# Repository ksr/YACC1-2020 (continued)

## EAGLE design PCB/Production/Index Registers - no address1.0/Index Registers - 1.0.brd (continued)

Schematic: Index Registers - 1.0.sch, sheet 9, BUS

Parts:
PWR: LED5MM
R1: 330; 0207/10
X1: FABC96R

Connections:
-AC-LD: X1.C22
-AC-LD-INV: X1.C20
-AC-RD: X1.C21
-ADDR-REG-LD0: X1.C4
-ADDR-REG-LD1: X1.C6
-ADDR-REG-RD0: X1.C3
-ADDR-REG-RD1: X1.C5
-ALU-FUNC: X1.C15
-BUS-EN: X1.C28; also elsewhere on the board
-HL-SWAP: X1.C25; also elsewhere on the board
-INT: X1.C13
-INTA: X1.C14
-IO-ADDR-LD: X1.C11
-IO-RD: X1.B25
-IO-WR: X1.B26
-MEM-RD: X1.B23
-MEM-WR: X1.B24
-REG-DN: X1.B21; also elsewhere on the board
-REG-FUNC-LD: X1.B8; also elsewhere on the board
-REG-FUNC-RD: X1.B7; also elsewhere on the board
-REG-LD-HI: X1.B20; also elsewhere on the board
-REG-LD-LO: X1.B18; also elsewhere on the board
-REG-RD-HI: X1.B19; also elsewhere on the board
-REG-RD-LO: X1.B17; also elsewhere on the board
-REG-UP: X1.B22; also elsewhere on the board
-RESET: X1.C30; also elsewhere on the board
-RUN: X1.C29
-SR-LD: X1.C23
-TMP-REG-LD0: X1.B28
-TMP-REG-LD1: X1.B30
-TMP-REG-RD0: X1.B27
-TMP-REG-RD1: X1.B29
ADDR0: X1.A3
ADDR1: X1.A4
ADDR2: X1.A5
ADDR3: X1.A6
ADDR4: X1.A7
ADDR5: X1.A8
ADDR6: X1.A9
ADDR7: X1.A10
ADDR8: X1.A11
ADDR9: X1.A12
ADDR10: X1.A13
ADDR11: X1.A14
ADDR12: X1.A15
ADDR13: X1.A16
ADDR14: X1.A17
ADDR15: X1.A18
ALU0: X1.C16
ALU1: X1.C17
ALU2: X1.C18
ALU3: X1.C19
BR-COND: X1.C24
DATA0: X1.A19; also elsewhere on the board
DATA1: X1.A20; also elsewhere on the board
DATA2: X1.A21; also elsewhere on the board
DATA3: X1.A22; also elsewhere on the board
DATA4: X1.A23; also elsewhere on the board
DATA5: X1.A24; also elsewhere on the board
DATA6: X1.A25; also elsewhere on the board
DATA7: X1.A26; also elsewhere on the board
DATA8: X1.A27; also elsewhere on the board
DATA9: X1.A28; also elsewhere on the board
DATA10: X1.A29; also elsewhere on the board
DATA11: X1.A30; also elsewhere on the board
DATA12: X1.B3; also elsewhere on the board
DATA13: X1.B4; also elsewhere on the board
DATA14: X1.B5; also elsewhere on the board
DATA15: X1.B6; also elsewhere on the board
GND: PWR.K (C), X1.A1, X1.A32, X1.B1, X1.B32, X1.C1, X1.C32; also elsewhere on the board
IN: X1.C26
IO-ADDR0: X1.C7
IO-ADDR1: X1.C8
IO-ADDR2: X1.C9
IO-ADDR3: X1.C10
unnamed: PWR.A, R1.1
OUT: X1.C27
REG-LD-ID0: X1.B13; also elsewhere on the board
REG-LD-ID1: X1.B14; also elsewhere on the board
REG-LD-ID2: X1.B15; also elsewhere on the board
REG-LD-ID3: X1.B16; also elsewhere on the board
REG-RD-ID0: X1.B9; also elsewhere on the board
REG-RD-ID1: X1.B10; also elsewhere on the board
REG-RD-ID2: X1.B11; also elsewhere on the board
REG-RD-ID3: X1.B12; also elsewhere on the board
UNUSED0: X1.C12
VCC: R1.2, X1.A2, X1.A31, X1.B2, X1.B31, X1.C2, X1.C31; also elsewhere on the board

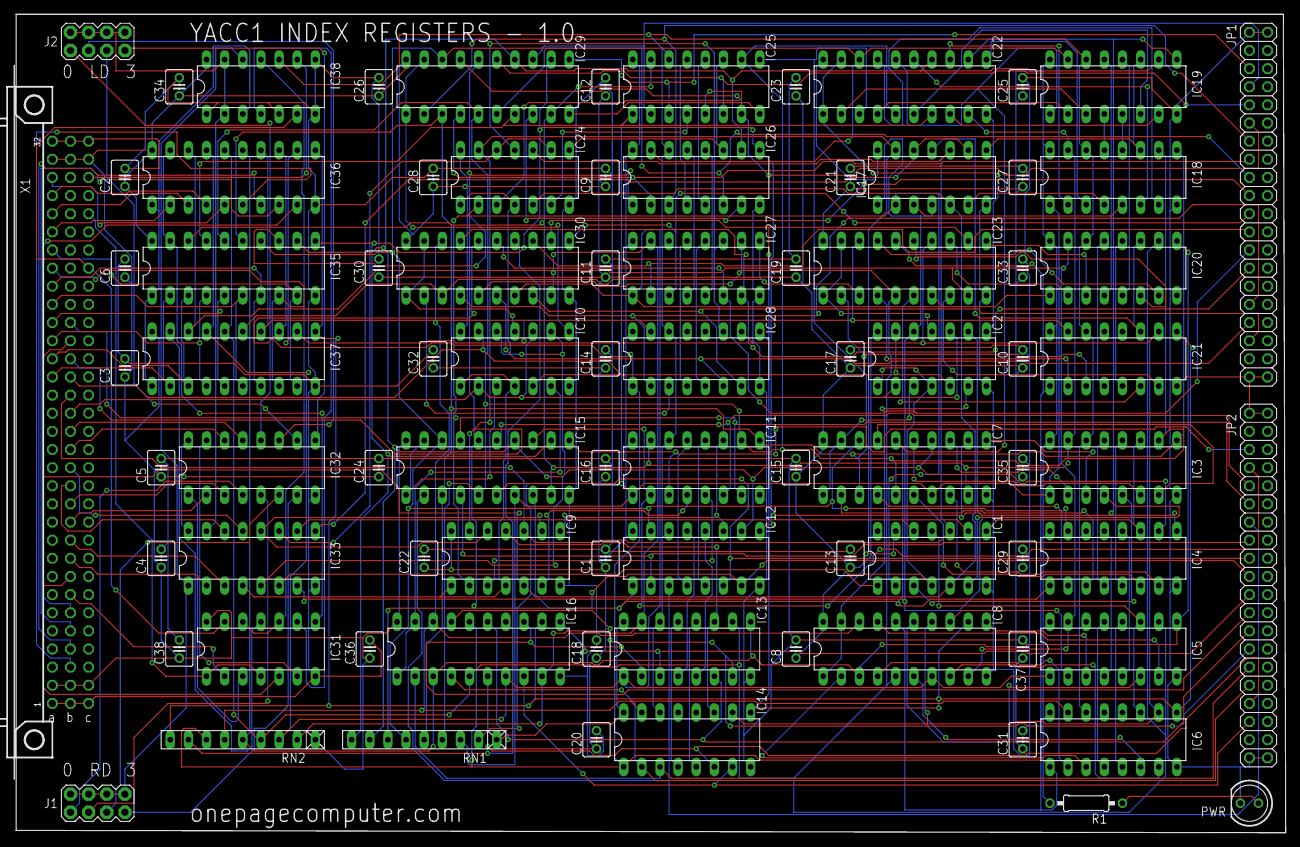
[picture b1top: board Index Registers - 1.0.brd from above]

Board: 2 copper layers, 177.8 x 114.6 mm, 83 parts (0 on the bottom side), 192 nets.

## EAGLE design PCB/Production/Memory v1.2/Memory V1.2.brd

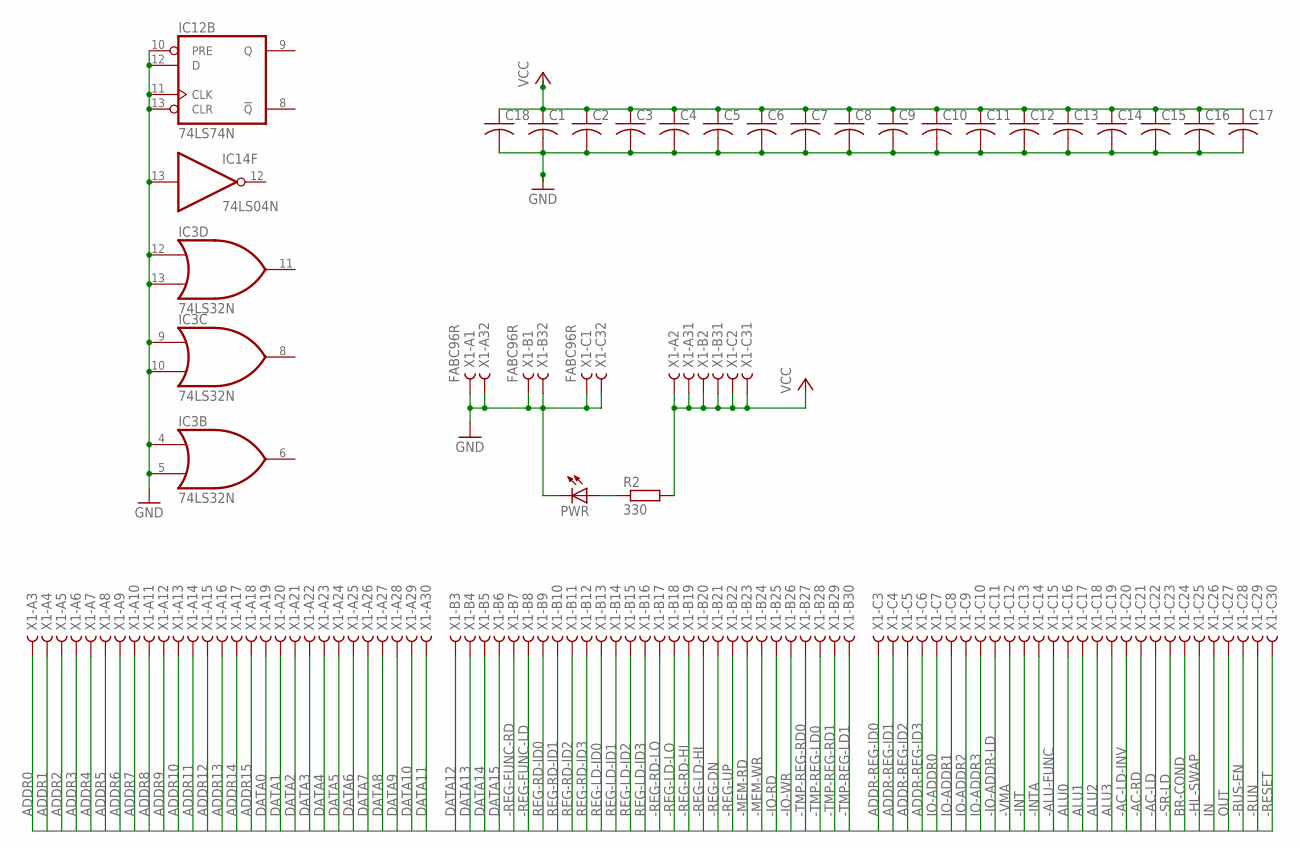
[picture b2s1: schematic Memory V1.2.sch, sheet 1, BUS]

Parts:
C1, C2, C3, C4, C5, C6, C7, C8, C9, C10, C11, C12, C13, C14, C15, C16, C17, C18: C-US025-025X050; C025-025X050
IC3: 74LS32N; DIL14
IC12: 74LS74N; DIL14
IC14: 74LS04N; DIL14
PWR: LED5MM
R2: 330; 0207/10
X1: FABC96R

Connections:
-AC-LD: X1.C22
-AC-LD-INV: X1.C20
-AC-RD: X1.C21
-ALU-FUNC: X1.C15
-BUS-EN: X1.C28; also elsewhere on the board
-HL-SWAP: X1.C25
-INT: X1.C13
-INTA: X1.C14
-IO-ADDR-LD: X1.C11
-IO-RD: X1.B25
-IO-WR: X1.B26
-MEM-RD: X1.B23; also elsewhere on the board
-MEM-WR: X1.B24; also elsewhere on the board
-REG-DN: X1.B21
-REG-FUNC-LD: X1.B8
-REG-FUNC-RD: X1.B7
-REG-LD-HI: X1.B20
-REG-LD-LO: X1.B18
-REG-RD-HI: X1.B19
-REG-RD-LO: X1.B17
-REG-UP: X1.B22
-RESET: X1.C30; also elsewhere on the board
-RUN: X1.C29
-SR-LD: X1.C23
-TMP-REG-LD0: X1.B28; also elsewhere on the board
-TMP-REG-LD1: X1.B30; also elsewhere on the board
-TMP-REG-RD0: X1.B27; also elsewhere on the board
-TMP-REG-RD1: X1.B29; also elsewhere on the board
-VMA: X1.C12; also elsewhere on the board
ADDR0: X1.A3; also elsewhere on the board
ADDR1: X1.A4; also elsewhere on the board
ADDR2: X1.A5; also elsewhere on the board
ADDR3: X1.A6; also elsewhere on the board
ADDR4: X1.A7; also elsewhere on the board
ADDR5: X1.A8; also elsewhere on the board
ADDR6: X1.A9; also elsewhere on the board
ADDR7: X1.A10; also elsewhere on the board
ADDR8: X1.A11; also elsewhere on the board
ADDR9: X1.A12; also elsewhere on the board
ADDR10: X1.A13; also elsewhere on the board
ADDR11: X1.A14; also elsewhere on the board
ADDR12: X1.A15; also elsewhere on the board
ADDR13: X1.A16; also elsewhere on the board
ADDR14: X1.A17; also elsewhere on the board
ADDR15: X1.A18; also elsewhere on the board
ADDR-REG-ID0: X1.C3
ADDR-REG-ID1: X1.C4
ADDR-REG-ID2: X1.C5
ADDR-REG-ID3: X1.C6
ALU0: X1.C16
ALU1: X1.C17
ALU2: X1.C18
ALU3: X1.C19
BR-COND: X1.C24
DATA0: X1.A19; also elsewhere on the board
DATA1: X1.A20; also elsewhere on the board
DATA2: X1.A21; also elsewhere on the board
DATA3: X1.A22; also elsewhere on the board
DATA4: X1.A23; also elsewhere on the board
DATA5: X1.A24; also elsewhere on the board
DATA6: X1.A25; also elsewhere on the board
DATA7: X1.A26; also elsewhere on the board
DATA8: X1.A27; also elsewhere on the board
DATA9: X1.A28; also elsewhere on the board
DATA10: X1.A29; also elsewhere on the board
DATA11: X1.A30; also elsewhere on the board
DATA12: X1.B3; also elsewhere on the board
DATA13: X1.B4; also elsewhere on the board
DATA14: X1.B5; also elsewhere on the board
DATA15: X1.B6; also elsewhere on the board
GND: C1.2, C2.2, C3.2, C4.2, C5.2, C6.2, C7.2, C8.2, C9.2, C10.2, C11.2, C12.2, C13.2, C14.2, C15.2, C16.2, C17.2, C18.2, IC3.4 (I0), IC3.5 (I1), IC3.7 (GND), IC3.9 (I0), IC3.10 (I1), IC3.12 (I0), IC3.13 (I1), IC12.7 (GND), IC12.10 (PRE), IC12.11 (CLK), IC12.12 (D), IC12.13 (CLR), IC14.7 (GND), IC14.13 (I), PWR.K (C), X1.A1, X1.A32, X1.B1, X1.B32, X1.C1, X1.C32; also elsewhere on the board
IN: X1.C26
IO-ADDR0: X1.C7
IO-ADDR1: X1.C8
IO-ADDR2: X1.C9
IO-ADDR3: X1.C10
unnamed: PWR.A, R2.1
OUT: X1.C27
REG-LD-ID0: X1.B13
REG-LD-ID1: X1.B14
REG-LD-ID2: X1.B15
REG-LD-ID3: X1.B16
REG-RD-ID0: X1.B9
REG-RD-ID1: X1.B10
REG-RD-ID2: X1.B11
REG-RD-ID3: X1.B12
VCC: C1.1, C2.1, C3.1, C4.1, C5.1, C6.1, C7.1, C8.1, C9.1, C10.1, C11.1, C12.1, C13.1, C14.1, C15.1, C16.1, C17.1, C18.1, IC3.14 (VCC), IC12.14 (VCC), IC14.14 (VCC), R2.2, X1.A2, X1.A31, X1.B2, X1.B31, X1.C2, X1.C31; also elsewhere on the board

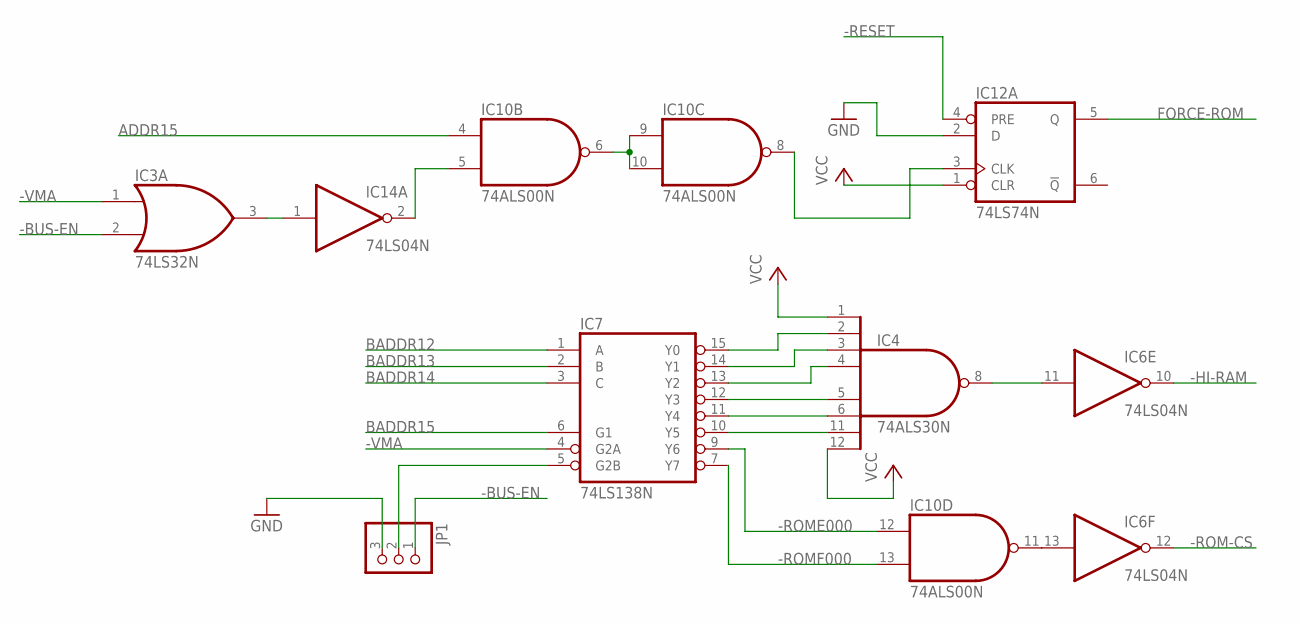
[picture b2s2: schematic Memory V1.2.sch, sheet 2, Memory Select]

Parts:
IC3: 74LS32N; DIL14
IC4: 74ALS30N; DIL14
IC6, IC14: 74LS04N; DIL14
IC7: 74LS138N; DIL16
IC10: 74ALS00N; DIL14
IC12: 74LS74N; DIL14
JP1: PINHD-1X3; 1X03

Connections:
-BUS-EN: IC3.2 (I1), JP1.1; also elsewhere on the board
-HI-RAM: IC6.10 (O); also elsewhere on the board
-RESET: IC12.4 (PRE); also elsewhere on the board
-ROM-CS: IC6.12 (O); also elsewhere on the board
-ROME000: IC7.9 (Y6), IC10.12 (I0)
-ROMF000: IC7.7 (Y7), IC10.13 (I1)
-VMA: IC3.1 (I0), IC7.4 (G2A); also elsewhere on the board
ADDR15: IC10.4 (I0); also elsewhere on the board
BADDR12: IC7.1 (A); also elsewhere on the board
BADDR13: IC7.2 (B); also elsewhere on the board
BADDR14: IC7.3 (C); also elsewhere on the board
BADDR15: IC7.6 (G1); also elsewhere on the board
FORCE-ROM: IC12.5 (Q); also elsewhere on the board
GND: IC3.7 (GND), IC4.7 (GND), IC6.7 (GND), IC7.8 (GND), IC10.7 (GND), IC12.2 (D), IC12.7 (GND), IC14.7 (GND), JP1.3; also elsewhere on the board
unnamed: IC6.13 (I), IC10.11 (O)
unnamed: IC4.11 (I6), IC7.10 (Y5)
unnamed: IC4.6 (I5), IC7.11 (Y4)
unnamed: IC4.5 (I4), IC7.12 (Y3)
unnamed: IC4.4 (I3), IC7.13 (Y2)
unnamed: IC4.3 (I2), IC7.14 (Y1)
unnamed: IC4.2 (I1), IC7.15 (Y0)
unnamed: IC4.8 (O), IC6.11 (I)
unnamed: IC10.8 (O), IC12.3 (CLK)
unnamed: IC10.6 (O), IC10.9 (I0), IC10.10 (I1)
unnamed: IC10.5 (I1), IC14.2 (O)
unnamed: IC7.5 (G2B), JP1.2
unnamed: IC3.3 (O), IC14.1 (I)
VCC: IC3.14 (VCC), IC4.1 (I0), IC4.12 (I7), IC4.14 (VCC), IC6.14 (VCC), IC7.16 (VCC), IC10.14 (VCC), IC12.1 (CLR), IC12.14 (VCC), IC14.14 (VCC); also elsewhere on the board

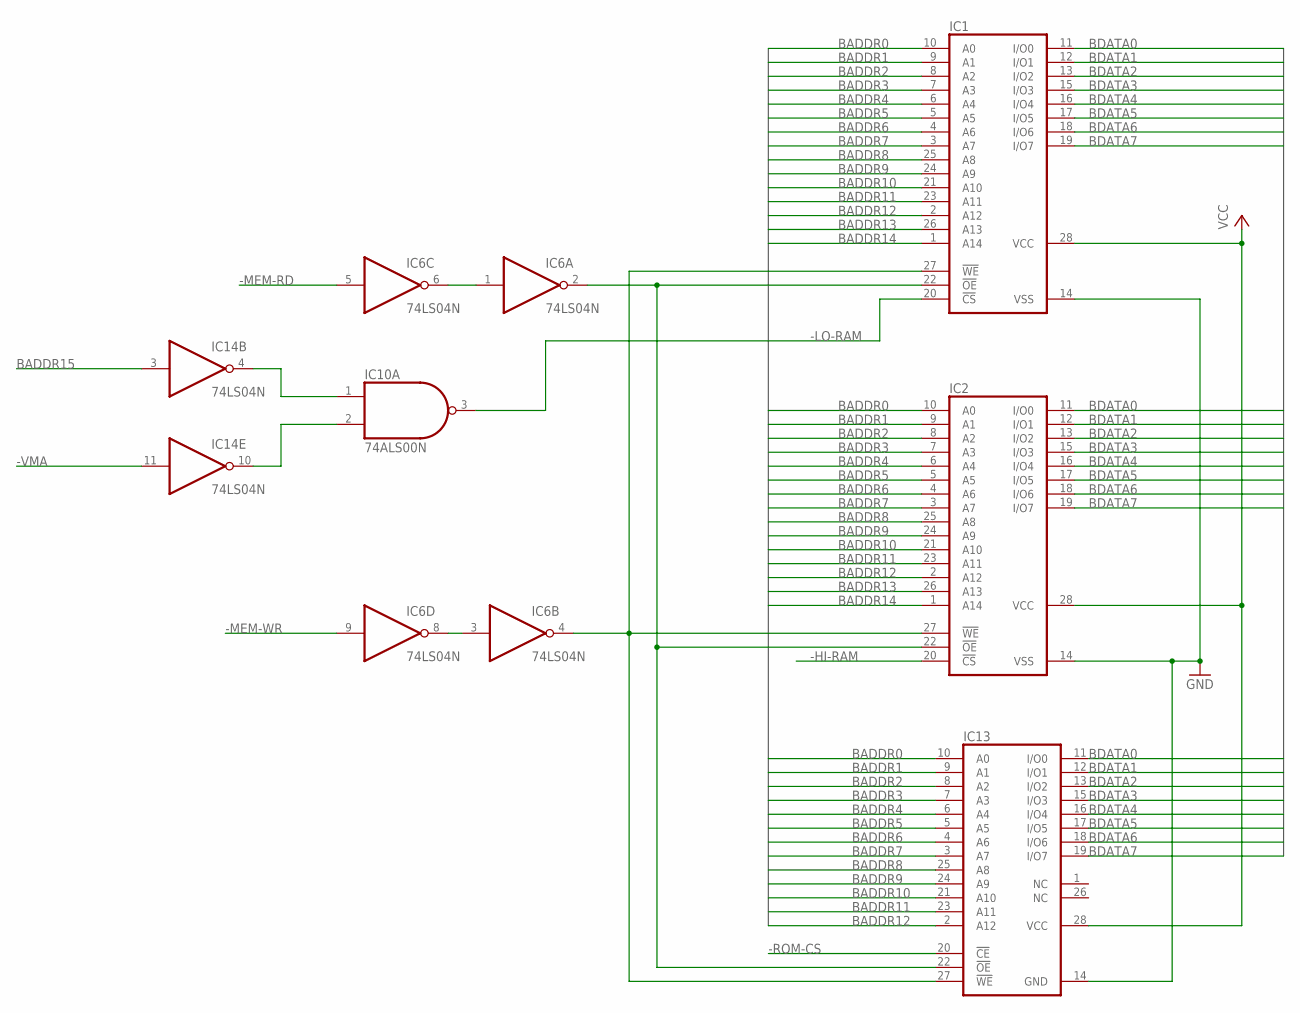
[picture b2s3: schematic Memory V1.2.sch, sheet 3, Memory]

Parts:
IC1, IC2: 62256P; DIL28-6
IC6, IC14: 74LS04N; DIL14
IC10: 74ALS00N; DIL14
IC13: 28C64C; DIL28-6

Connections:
-HI-RAM: IC2.20 (!CS); also elsewhere on the board
-LO-RAM: IC1.20 (!CS), IC10.3 (O)
-MEM-RD: IC6.5 (I); also elsewhere on the board
-MEM-WR: IC6.9 (I); also elsewhere on the board
-ROM-CS: IC13.20 (!CE); also elsewhere on the board
-VMA: IC14.11 (I); also elsewhere on the board
BADDR0: IC1.10 (A0), IC2.10 (A0), IC13.10 (A0); also elsewhere on the board
BADDR1: IC1.9 (A1), IC2.9 (A1), IC13.9 (A1); also elsewhere on the board
BADDR2: IC1.8 (A2), IC2.8 (A2), IC13.8 (A2); also elsewhere on the board
BADDR3: IC1.7 (A3), IC2.7 (A3), IC13.7 (A3); also elsewhere on the board
BADDR4: IC1.6 (A4), IC2.6 (A4), IC13.6 (A4); also elsewhere on the board
BADDR5: IC1.5 (A5), IC2.5 (A5), IC13.5 (A5); also elsewhere on the board
BADDR6: IC1.4 (A6), IC2.4 (A6), IC13.4 (A6); also elsewhere on the board
BADDR7: IC1.3 (A7), IC2.3 (A7), IC13.3 (A7); also elsewhere on the board
BADDR8: IC1.25 (A8), IC2.25 (A8), IC13.25 (A8); also elsewhere on the board
BADDR9: IC1.24 (A9), IC2.24 (A9), IC13.24 (A9); also elsewhere on the board
BADDR10: IC1.21 (A10), IC2.21 (A10), IC13.21 (A10); also elsewhere on the board
BADDR11: IC1.23 (A11), IC2.23 (A11), IC13.23 (A11); also elsewhere on the board
BADDR12: IC1.2 (A12), IC2.2 (A12), IC13.2 (A12); also elsewhere on the board
BADDR13: IC1.26 (A13), IC2.26 (A13); also elsewhere on the board
BADDR14: IC1.1 (A14), IC2.1 (A14); also elsewhere on the board
BADDR15: IC14.3 (I); also elsewhere on the board
BDATA0: IC1.11 (I/O0), IC2.11 (I/O0), IC13.11 (I/O0); also elsewhere on the board
BDATA1: IC1.12 (I/O1), IC2.12 (I/O1), IC13.12 (I/O1); also elsewhere on the board
BDATA2: IC1.13 (I/O2), IC2.13 (I/O2), IC13.13 (I/O2); also elsewhere on the board
BDATA3: IC1.15 (I/O3), IC2.15 (I/O3), IC13.15 (I/O3); also elsewhere on the board
BDATA4: IC1.16 (I/O4), IC2.16 (I/O4), IC13.16 (I/O4); also elsewhere on the board
BDATA5: IC1.17 (I/O5), IC2.17 (I/O5), IC13.17 (I/O5); also elsewhere on the board
BDATA6: IC1.18 (I/O6), IC2.18 (I/O6), IC13.18 (I/O6); also elsewhere on the board
BDATA7: IC1.19 (I/O7), IC2.19 (I/O7), IC13.19 (I/O7); also elsewhere on the board
GND: IC1.14 (VSS), IC2.14 (VSS), IC6.7 (GND), IC10.7 (GND), IC13.14 (GND), IC14.7 (GND); also elsewhere on the board
MEM-RD: IC6.1 (I), IC6.6 (O)
unnamed: IC6.3 (I), IC6.8 (O)
unnamed: IC1.22 (!OE), IC2.22 (!OE), IC6.2 (O), IC13.22 (!OE)
unnamed: IC1.27 (!WE), IC2.27 (!WE), IC6.4 (O), IC13.27 (!WE)
unnamed: IC10.2 (I1), IC14.10 (O)
unnamed: IC10.1 (I0), IC14.4 (O)
VCC: IC1.28 (VCC), IC2.28 (VCC), IC6.14 (VCC), IC10.14 (VCC), IC13.28 (VCC), IC14.14 (VCC); also elsewhere on the board

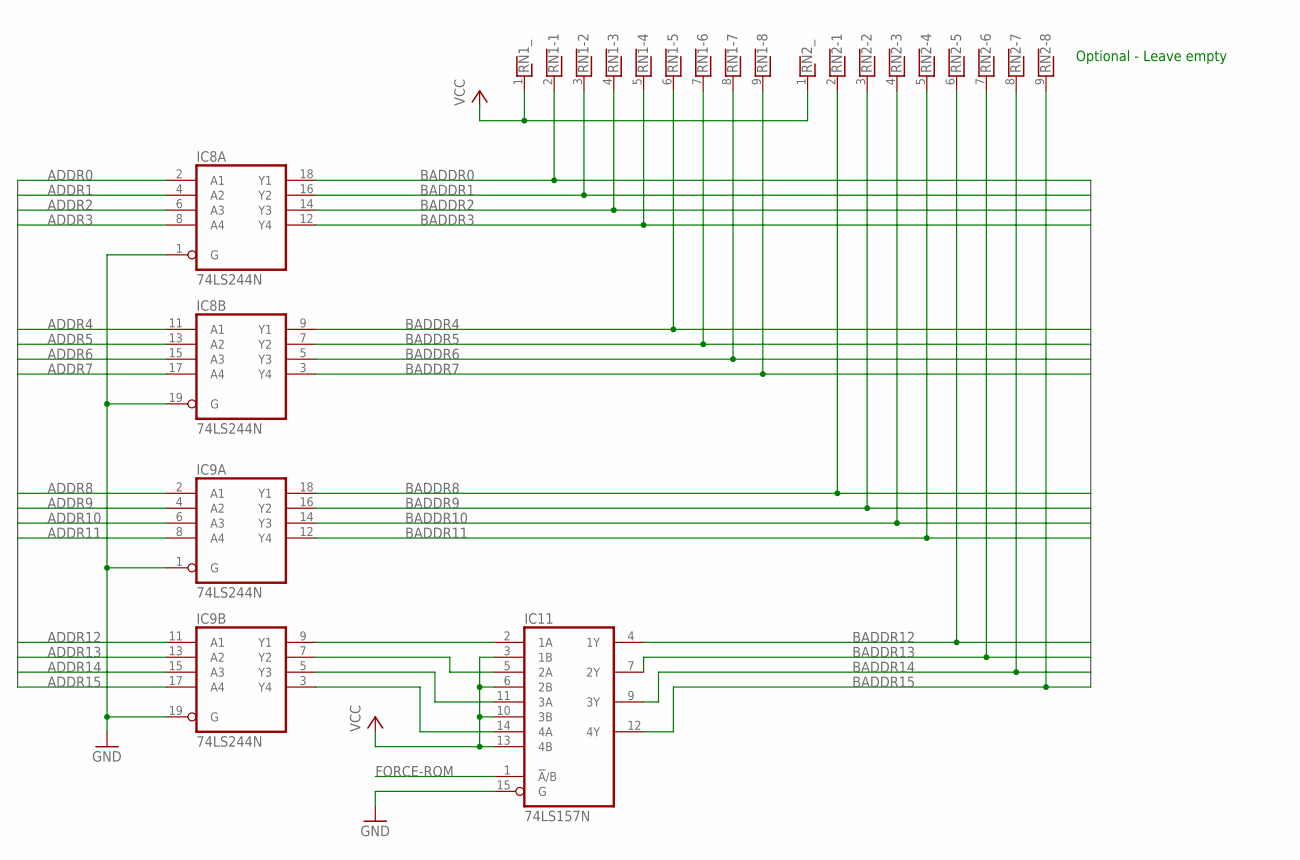
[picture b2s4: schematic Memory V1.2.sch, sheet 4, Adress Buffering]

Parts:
IC8, IC9: 74LS244N; DIL20
IC11: 74LS157N; DIL16
RN1, RN2: RNX8; RN-9

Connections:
ADDR0: IC8.2 (A1); also elsewhere on the board
ADDR1: IC8.4 (A2); also elsewhere on the board
ADDR2: IC8.6 (A3); also elsewhere on the board
ADDR3: IC8.8 (A4); also elsewhere on the board
ADDR4: IC8.11 (A1); also elsewhere on the board
ADDR5: IC8.13 (A2); also elsewhere on the board
ADDR6: IC8.15 (A3); also elsewhere on the board
ADDR7: IC8.17 (A4); also elsewhere on the board
ADDR8: IC9.2 (A1); also elsewhere on the board
ADDR9: IC9.4 (A2); also elsewhere on the board
ADDR10: IC9.6 (A3); also elsewhere on the board
ADDR11: IC9.8 (A4); also elsewhere on the board
ADDR12: IC9.11 (A1); also elsewhere on the board
ADDR13: IC9.13 (A2); also elsewhere on the board
ADDR14: IC9.15 (A3); also elsewhere on the board
ADDR15: IC9.17 (A4); also elsewhere on the board
BADDR0: IC8.18 (Y1), RN1.2; also elsewhere on the board
BADDR1: IC8.16 (Y2), RN1.3; also elsewhere on the board
BADDR2: IC8.14 (Y3), RN1.4; also elsewhere on the board
BADDR3: IC8.12 (Y4), RN1.5; also elsewhere on the board
BADDR4: IC8.9 (Y1), RN1.6; also elsewhere on the board
BADDR5: IC8.7 (Y2), RN1.7; also elsewhere on the board
BADDR6: IC8.5 (Y3), RN1.8; also elsewhere on the board
BADDR7: IC8.3 (Y4), RN1.9; also elsewhere on the board
BADDR8: IC9.18 (Y1), RN2.2; also elsewhere on the board
BADDR9: IC9.16 (Y2), RN2.3; also elsewhere on the board
BADDR10: IC9.14 (Y3), RN2.4; also elsewhere on the board
BADDR11: IC9.12 (Y4), RN2.5; also elsewhere on the board
BADDR12: IC11.4 (1Y), RN2.6; also elsewhere on the board
BADDR13: IC11.7 (2Y), RN2.7; also elsewhere on the board
BADDR14: IC11.9 (3Y), RN2.8; also elsewhere on the board
BADDR15: IC11.12 (4Y), RN2.9; also elsewhere on the board
FORCE-ROM: IC11.1 (!A!/B); also elsewhere on the board
GND: IC8.1 (G), IC8.10 (GND), IC8.19 (G), IC9.1 (G), IC9.10 (GND), IC9.19 (G), IC11.8 (GND), IC11.15 (G); also elsewhere on the board
unnamed: IC9.9 (Y1), IC11.2 (1A)
unnamed: IC9.7 (Y2), IC11.5 (2A)
unnamed: IC9.5 (Y3), IC11.11 (3A)
unnamed: IC9.3 (Y4), IC11.14 (4A)
VCC: IC8.20 (VCC), IC9.20 (VCC), IC11.3 (1B), IC11.6 (2B), IC11.10 (3B), IC11.13 (4B), IC11.16 (VCC), RN1.1, RN2.1; also elsewhere on the board

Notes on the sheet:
Optional - Leave empty

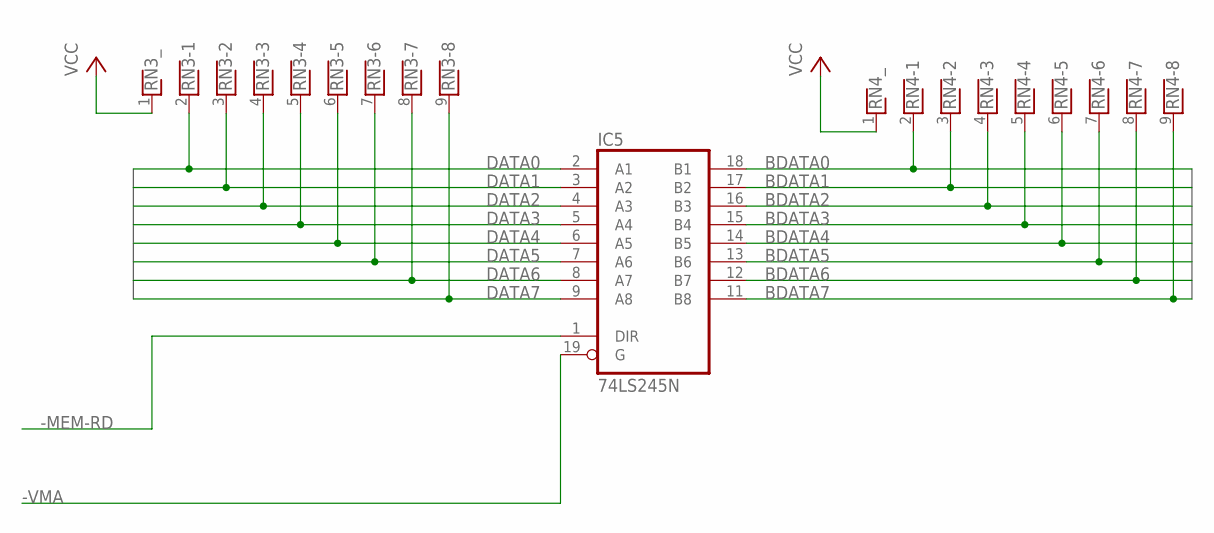
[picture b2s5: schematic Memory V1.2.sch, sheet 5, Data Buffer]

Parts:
IC5: 74LS245N; DIL20
RN3, RN4: RNX8; RN-9

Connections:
-MEM-RD: IC5.1 (DIR); also elsewhere on the board
-VMA: IC5.19 (G); also elsewhere on the board
BDATA0: IC5.18 (B1), RN4.2; also elsewhere on the board
BDATA1: IC5.17 (B2), RN4.3; also elsewhere on the board
BDATA2: IC5.16 (B3), RN4.4; also elsewhere on the board
BDATA3: IC5.15 (B4), RN4.5; also elsewhere on the board
BDATA4: IC5.14 (B5), RN4.6; also elsewhere on the board
BDATA5: IC5.13 (B6), RN4.7; also elsewhere on the board
BDATA6: IC5.12 (B7), RN4.8; also elsewhere on the board
BDATA7: IC5.11 (B8), RN4.9; also elsewhere on the board
DATA0: IC5.2 (A1), RN3.2; also elsewhere on the board
DATA1: IC5.3 (A2), RN3.3; also elsewhere on the board
DATA2: IC5.4 (A3), RN3.4; also elsewhere on the board
DATA3: IC5.5 (A4), RN3.5; also elsewhere on the board
DATA4: IC5.6 (A5), RN3.6; also elsewhere on the board
DATA5: IC5.7 (A6), RN3.7; also elsewhere on the board
DATA6: IC5.8 (A7), RN3.8; also elsewhere on the board
DATA7: IC5.9 (A8), RN3.9; also elsewhere on the board
GND: IC5.10 (GND); also elsewhere on the board
VCC: IC5.20 (VCC), RN3.1, RN4.1; also elsewhere on the board

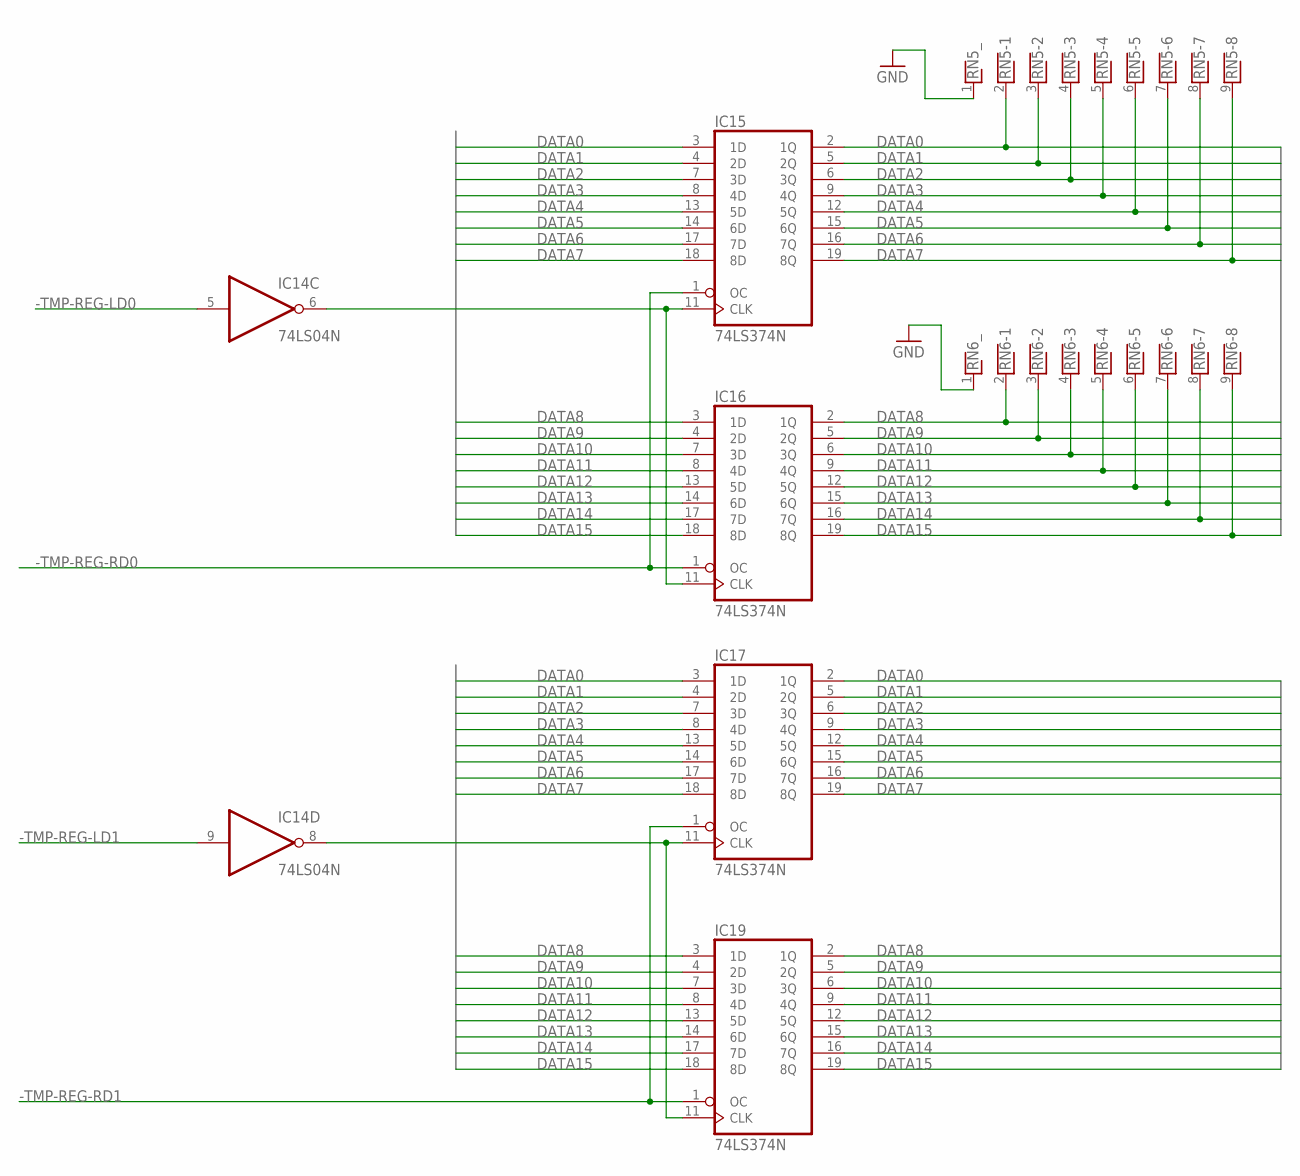
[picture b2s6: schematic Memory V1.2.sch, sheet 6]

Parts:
IC14: 74LS04N; DIL14
IC15, IC16, IC17, IC19: 74LS374N; DIL20
RN5, RN6: RNX8; RN-9

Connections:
-TMP-REG-LD0: IC14.5 (I); also elsewhere on the board
-TMP-REG-LD1: IC14.9 (I); also elsewhere on the board
-TMP-REG-RD0: IC15.1 (OC), IC16.1 (OC); also elsewhere on the board
-TMP-REG-RD1: IC17.1 (OC), IC19.1 (OC); also elsewhere on the board
DATA0: IC15.2 (1Q), IC15.3 (1D), IC17.2 (1Q), IC17.3 (1D), RN5.2; also elsewhere on the board
DATA1: IC15.4 (2D), IC15.5 (2Q), IC17.4 (2D), IC17.5 (2Q), RN5.3; also elsewhere on the board
DATA2: IC15.6 (3Q), IC15.7 (3D), IC17.6 (3Q), IC17.7 (3D), RN5.4; also elsewhere on the board
DATA3: IC15.8 (4D), IC15.9 (4Q), IC17.8 (4D), IC17.9 (4Q), RN5.5; also elsewhere on the board
DATA4: IC15.12 (5Q), IC15.13 (5D), IC17.12 (5Q), IC17.13 (5D), RN5.6; also elsewhere on the board
DATA5: IC15.14 (6D), IC15.15 (6Q), IC17.14 (6D), IC17.15 (6Q), RN5.7; also elsewhere on the board
DATA6: IC15.16 (7Q), IC15.17 (7D), IC17.16 (7Q), IC17.17 (7D), RN5.8; also elsewhere on the board
DATA7: IC15.18 (8D), IC15.19 (8Q), IC17.18 (8D), IC17.19 (8Q), RN5.9; also elsewhere on the board
DATA8: IC16.2 (1Q), IC16.3 (1D), IC19.2 (1Q), IC19.3 (1D), RN6.2; also elsewhere on the board
DATA9: IC16.4 (2D), IC16.5 (2Q), IC19.4 (2D), IC19.5 (2Q), RN6.3; also elsewhere on the board
DATA10: IC16.6 (3Q), IC16.7 (3D), IC19.6 (3Q), IC19.7 (3D), RN6.4; also elsewhere on the board
DATA11: IC16.8 (4D), IC16.9 (4Q), IC19.8 (4D), IC19.9 (4Q), RN6.5; also elsewhere on the board
DATA12: IC16.12 (5Q), IC16.13 (5D), IC19.12 (5Q), IC19.13 (5D), RN6.6; also elsewhere on the board
DATA13: IC16.14 (6D), IC16.15 (6Q), IC19.14 (6D), IC19.15 (6Q), RN6.7; also elsewhere on the board
DATA14: IC16.16 (7Q), IC16.17 (7D), IC19.16 (7Q), IC19.17 (7D), RN6.8; also elsewhere on the board
DATA15: IC16.18 (8D), IC16.19 (8Q), IC19.18 (8D), IC19.19 (8Q), RN6.9; also elsewhere on the board
GND: IC14.7 (GND), IC15.10 (GND), IC16.10 (GND), IC17.10 (GND), IC19.10 (GND), RN5.1, RN6.1; also elsewhere on the board
unnamed: IC14.6 (O), IC15.11 (CLK), IC16.11 (CLK)
unnamed: IC14.8 (O), IC17.11 (CLK), IC19.11 (CLK)
VCC: IC14.14 (VCC), IC15.20 (VCC), IC16.20 (VCC), IC17.20 (VCC), IC19.20 (VCC); also elsewhere on the board

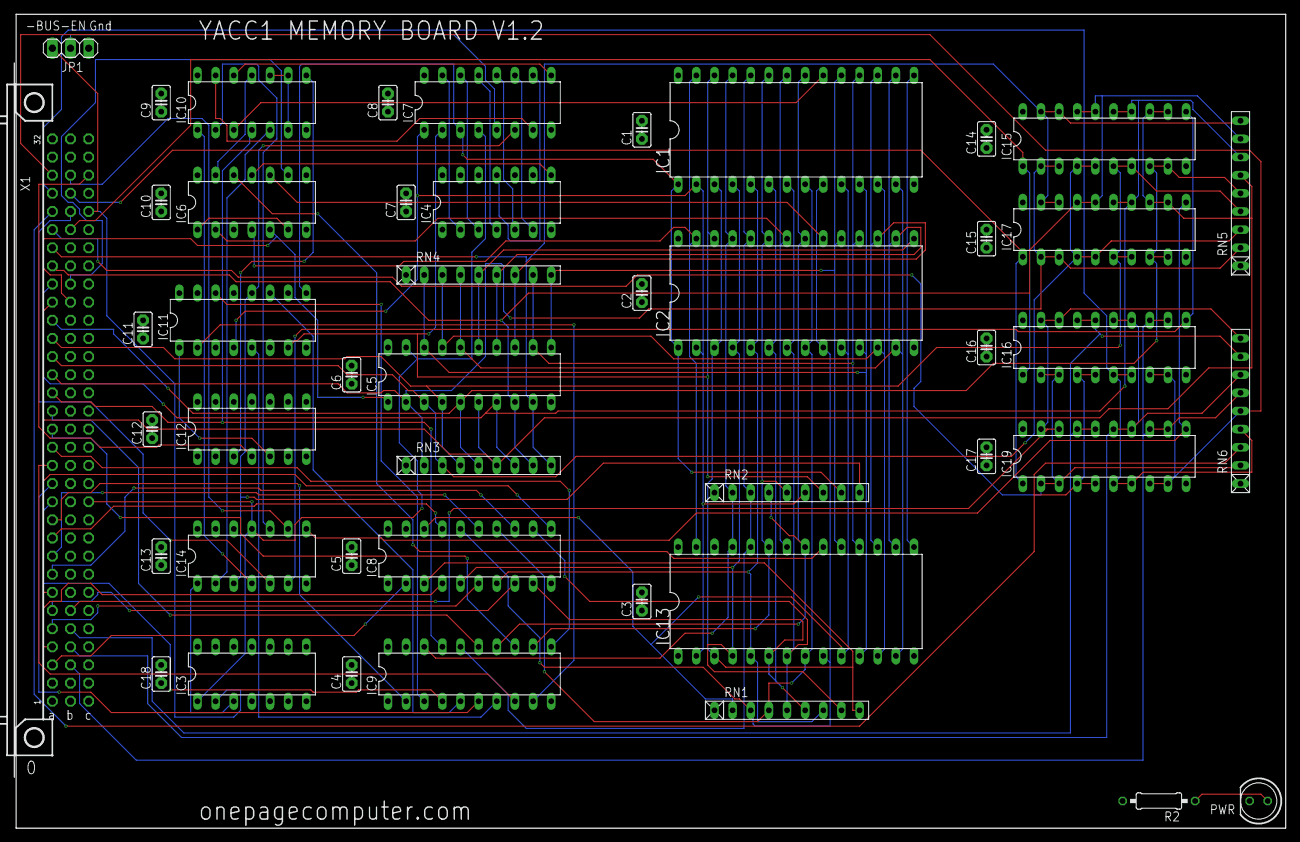
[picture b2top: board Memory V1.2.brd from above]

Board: 4 copper layers, 177.8 x 114.0 mm, 46 parts (0 on the bottom side), 99 nets.
